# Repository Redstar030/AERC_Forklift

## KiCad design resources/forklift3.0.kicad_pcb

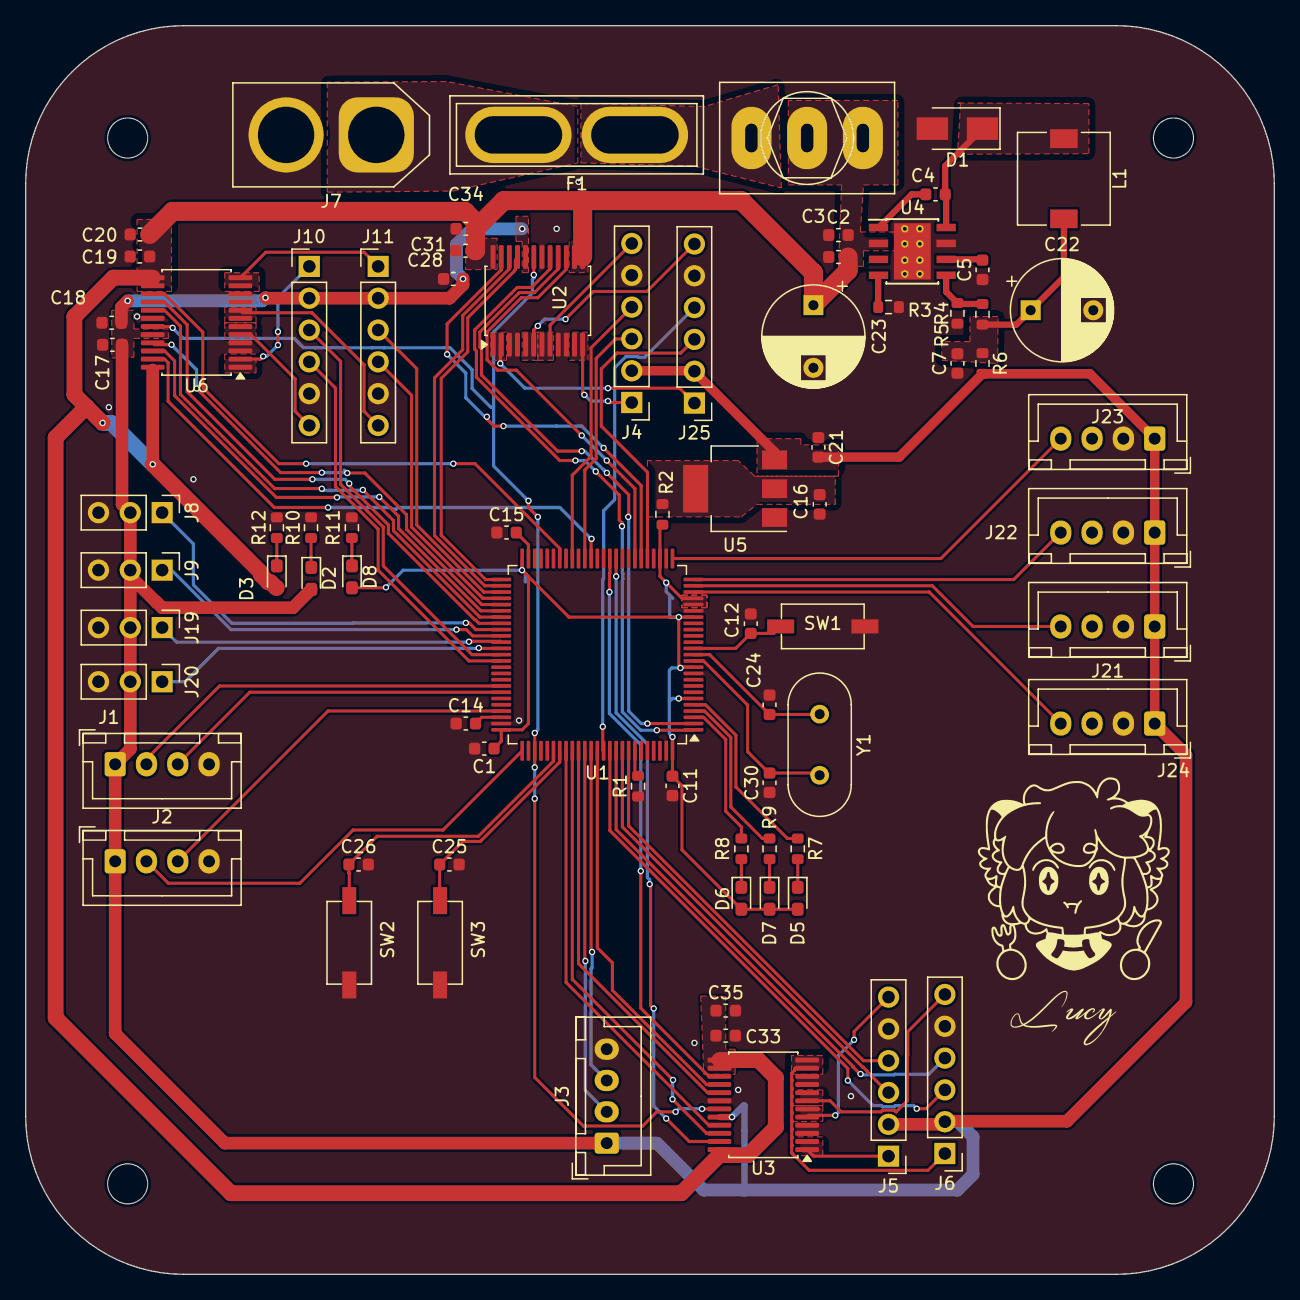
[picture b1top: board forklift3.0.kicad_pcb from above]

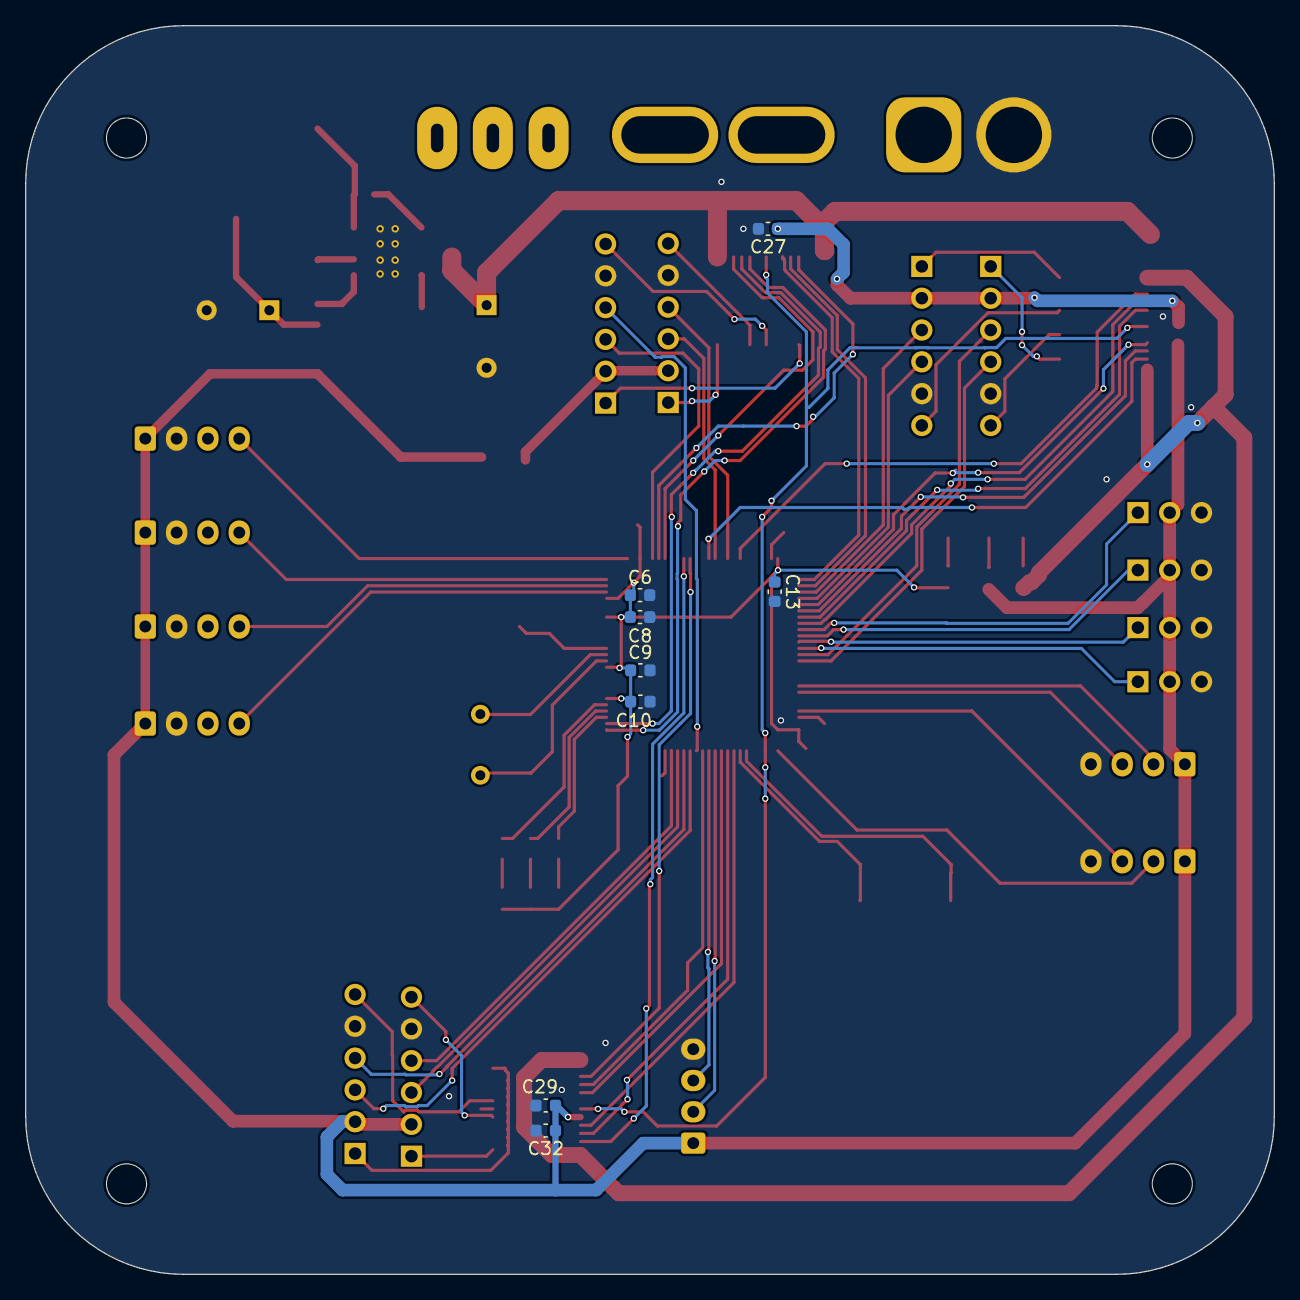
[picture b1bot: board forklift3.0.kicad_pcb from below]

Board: 2 copper layers, 99.7 x 99.7 mm, 89 parts (8 on the bottom side), 87 nets.

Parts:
C1, C4, C6, C8, C9, C10, C11, C12, C13, C25, C26: 100nF; C_0603_1608Metric
C2, C3, C14, C15: 2.2uF; C_0603_1608Metric
C5, C7: 39pF; C_0603_1608Metric
C16, C18, C20, C21, C28, C32, C34, C35: 10uF; C_0603_1608Metric
C17, C19, C27, C29, C31, C33: 0.1uF; C_0603_1608Metric
C22: 1MF; CP_Radial_D8.0mm_P12.00mm
C23: 50 100uF; CP_Radial_D8.0mm_P12.00mm
C24, C30: 20pF; C_0603_1608Metric
D1: SS54; D_SMA
D2: 5V; LED_0603_1608Metric_Pad1.05x0.95mm_HandSolder
D3: 12V; LED_0603_1608Metric_Pad1.05x0.95mm_HandSolder
D5: LED1; LED_0603_1608Metric_Pad1.05x0.95mm_HandSolder
D6: LED3; LED_0603_1608Metric_Pad1.05x0.95mm_HandSolder
D7: LED4; LED_0603_1608Metric_Pad1.05x0.95mm_HandSolder
D8: 3.3V; LED_0603_1608Metric_Pad1.05x0.95mm_HandSolder
F1: Fuse_Small; Fuse_Blade_ATO_directSolder
H1, H2, H3, H4: MountingHole; MountingHole_3.2mm_M3
J1, J2, J3, J21, J22, J23, J24: Conn_01x04; JST_XH_B4B-XH-A_1x04_P2.50mm_Vertical
J4, J5, J6, J10, J11, J25: Conn_01x06; PinHeader_1x06_P2.54mm_Vertical
J7: Conn_01x02; AMASS_XT60-M_1x02_P7.20mm_Vertical
J8, J9, J19, J20: Conn_01x03; PinHeader_1x03_P2.54mm_Vertical
L1: 22uH; L_7.3x7.3_H3.5
R1: 10K; R_0603_1608Metric
R2, R6: 0R; R_0603_1608Metric
R3: 162K; R_0603_1608Metric
R4: 53.6K; R_0603_1608Metric
R5: 10.2K; R_0603_1608Metric
R7, R8, R9, R10: 1.5K; R_0603_1608Metric
R11: 1K; R_0603_1608Metric
R12: 2K; R_0603_1608Metric
SW1: RST; SW_Push
SW2: But1; SW_Push
SW3: But2; SW_Push
SW4: SW_SPDT; SW_Toggle_Blue_wSlots
U1: STM32F407VETx; LQFP-100_14x14mm_P0.5mm
U2, U3, U6: TB6612FNG; SSOP-24_5.3x8.2mm_P0.65mm
U4: TPS54360DDA; TI_SO-PowerPAD-8_ThermalVias
U5: LM1117-3.3V; SOT-223
Y1: 8MHz; Crystal_HC49-4H_Vertical

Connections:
+3.3V: C1.1, C6.1, C8.1, C9.1, C10.1, C11.1, C13.1, D5.2 (A), D6.2 (A), D7.2 (A), D8.2 (A), R2.2, U1.6 (VBAT), U1.11 (VDD), U1.19 (VDD), U1.21 (VREF+), U1.22 (VDDA), U1.28 (VDD), U1.50 (VDD), U1.75 (VDD), U1.100 (VDD)
+5V: C17.1, C18.1, C21.2, C27.1, C28.1, C29.1, C32.1, D2.2 (A), J1.1, J2.1, J3.1, J4.2, J5.2, J6.2, J8.2, J9.2, J10.2, J11.2, J19.2, J20.2, J21.1, J22.1, J23.1, J24.1, J25.2, R6.2, U2.20 (VCC), U3.20 (VCC), U5.3 (VI), U6.20 (VCC)
+12V: C2.2, C3.2, C19.1, C20.1, C23.1, C31.1, C33.1, C34.1, C35.1, D3.2 (A), SW4.2 (B), SW4.3 (C), U2.13 (VM2), U2.14 (VM3), U2.24 (VM1), U3.13 (VM2), U3.14 (VM3), U3.24 (VM1), U4.2 (VIN), U6.13 (VM2), U6.14 (VM3), U6.24 (VM1)
/But1: C26.1, SW2.1, U1.81 (PD0)
/But2: C25.1, SW3.1, U1.82 (PD1)
/FB: R4.2, R5.1, U4.5 (FB)
/LED1: R7.1, U1.5 (PE6)
/LED3: R8.1, U1.3 (PE4)
/LED4: R9.1, U1.4 (PE5)
/M1_01: J25.1, U2.1 (AO1), U2.2 (AO1)
/M1_02: J25.6, U2.5 (AO2), U2.6 (AO2)
/M2_01: J4.1, U2.11 (BO1), U2.12 (BO1)
/M2_02: J4.6, U2.7 (BO2), U2.8 (BO2)
/M3_01: J5.1, U3.1 (AO1), U3.2 (AO1)
/M3_02: J5.6, U3.5 (AO2), U3.6 (AO2)
/M4_01: J6.1, U3.11 (BO1), U3.12 (BO1)
/M4_02: J6.6, U3.7 (BO2), U3.8 (BO2)
/M5_01: J10.1, U6.1 (AO1), U6.2 (AO1)
/M5_02: J10.6, U6.5 (AO2), U6.6 (AO2)
/M6_01: J11.1, U6.11 (BO1), U6.12 (BO1)
/M6_02: J11.6, U6.7 (BO2), U6.8 (BO2)
/PA0: J24.4, U1.23 (PA0)
/PA1: J21.4, U1.24 (PA1)
/PA2: J22.4, U1.25 (PA2)
/PA3: J23.4, U1.26 (PA3)
/PA5: J25.3, U1.30 (PA5)
/PB3: J25.4, U1.89 (PB3)
/PB4: J6.3, U1.90 (PB4)
/PB5: J6.4, U1.91 (PB5)
/PB6: J5.3, U1.92 (PB6)
/PB7: J5.4, U1.93 (PB7)
/PB12: U1.51 (PB12), U2.21 (AIN1)
/PB13: U1.52 (PB13), U2.22 (AIN2)
/PB14: J11.3, U1.53 (PB14)
/PB15: J11.4, U1.54 (PB15)
/PC6: J10.3, U1.63 (PC6)
/PC7: J10.4, U1.64 (PC7)
/PD2: U1.83 (PD2), U3.21 (AIN1)
/PD3: U1.84 (PD3), U3.22 (AIN2)
/PD4: U1.85 (PD4), U3.17 (BIN1)
/PD7: U1.88 (PD7), U3.16 (BIN2)
/PD8: U1.55 (PD8), U6.21 (AIN1)
/PD9: U1.56 (PD9), U6.22 (AIN2)
/PD10: U1.57 (PD10), U6.17 (BIN1)
/PD11: U1.58 (PD11), U6.16 (BIN2)
/PE2: U1.1 (PE2), U2.17 (BIN1)
/PE3: U1.2 (PE3), U2.16 (BIN2)
/PE9: J4.3, U1.40 (PE9)
/PE11: J4.4, U1.42 (PE11)
/PWM1: U1.31 (PA6), U2.23 (PWMA)
/PWM2: U1.32 (PA7), U2.15 (PWMB)
/PWM3: U1.35 (PB0), U3.23 (PWMA)
/PWM4: U1.36 (PB1), U3.15 (PWMB)
/PWM5: U1.39 (PE8), U6.23 (PWMA)
/PWM6: U1.44 (PE13), U6.15 (PWMB)
/PWMA: J8.1, U1.59 (PD12)
/PWMB: J9.1, U1.60 (PD13)
/PWMC: J19.1, U1.61 (PD14)
/PWMD: J20.1, U1.62 (PD15)
/STBY1: U1.78 (PC10), U2.19 (STBY), U3.19 (STBY), U6.19 (STBY)
/SWCLK: J2.2, U1.76 (PA14)
/SWDIO: J2.3, U1.72 (PA13)
/UART1_RX: J1.3, U1.69 (PA10)
/UART1_TX: J1.2, U1.68 (PA9)
/UART2_RX: J3.3, U1.87 (PD6)
/UART2_TX: J3.2, U1.86 (PD5)
GND: C1.2, C2.1, C3.1, C5.1, C6.2, C7.1, C8.2, C9.2, C10.2, C11.2, C12.1, C13.2, C14.1, C15.1, C16.1, C17.2, C18.2, C19.2, C20.2, C21.1, C22.2, C23.2, C24.1, C25.2, C26.2, C27.2, C28.2, C29.2, C30.1, C31.2, C32.2, C33.2, C34.2, C35.2, D1.2 (A), J1.4, J2.4, J3.4, J4.5, J5.5, J6.5, J7.2, J8.3, J9.3, J10.5, J11.5, J19.3, J20.3, J21.2, J22.2, J23.2, J24.2, J25.5, R1.1, R3.2, R5.2, R10.2, R11.2, R12.2, SW1.2, SW2.2, SW3.2, U1.10 (VSS), U1.20 (VSSA), U1.27 (VSS), U1.74 (VSS), U1.99 (VSS), U2.3 (PGND1), U2.4 (PGND1), U2.9 (PGND2), U2.10 (PGND2), U2.18 (GND), U3.3 (PGND1), U3.4 (PGND1), U3.9 (PGND2), U3.10 (PGND2), U3.18 (GND), U4.7 (GND), U4.9 (GNDPAD), U5.1 (GND), U6.3 (PGND1), U6.4 (PGND1), U6.9 (PGND2), U6.10 (PGND2), U6.18 (GND)
unnamed: C7.2, C22.1, L1.2, R4.1, R6.1
unnamed: C4.1, D1.1 (K), L1.1, U4.8 (SW)
unnamed: D2.1 (K), R10.1
unnamed: D3.1 (K), R12.1
unnamed: D5.1 (K), R7.2
unnamed: D6.1 (K), R8.2
unnamed: D7.1 (K), R9.2
unnamed: D8.1 (K), R11.1
unnamed: F1.2, J7.1
unnamed: F1.1, SW4.1 (A)
unnamed: R1.2, U1.94 (BOOT0)
unnamed: C12.2, SW1.1, U1.14 (NRST)
unnamed: C30.2, U1.12 (PH0), Y1.2
unnamed: C24.2, U1.13 (PH1), Y1.1
unnamed: C15.2, U1.49 (VCAP_1)
unnamed: C14.2, U1.73 (VCAP_2)
unnamed: C4.2, U4.1 (BOOT)
unnamed: C5.2, U4.6 (COMP)
unnamed: R3.1, U4.4 (RT/CLK)
unnamed: C16.2, R2.1, U5.2 (VO), U5.4 (Tab)

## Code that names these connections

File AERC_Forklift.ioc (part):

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Mcu.Name=STM32F407V(E-G)Tx
Mcu.Package=LQFP100
Mcu.UserName=STM32F407VETx
PA0-WKUP.GPIOParameters=GPIO_PuPd
PA0-WKUP.GPIO_PuPd=GPIO_PULLUP
PA0-WKUP.Signal=S_TIM5_CH1
PA1.GPIOParameters=GPIO_PuPd
PA1.GPIO_PuPd=GPIO_PULLUP
PA1.Signal=S_TIM5_CH2
PA10.Mode=Asynchronous
PA10.Signal=USART1_RX
PA13.Mode=Serial_Wire
PA13.Signal=SYS_JTMS-SWDIO
PA14.Mode=Serial_Wire
PA14.Signal=SYS_JTCK-SWCLK
PA5.GPIOParameters=GPIO_PuPd,GPIO_Label
PA5.GPIO_Label=ENC1A
PA5.GPIO_PuPd=GPIO_PULLUP
PA5.Signal=S_TIM2_CH1_ETR
PA6.GPIOParameters=GPIO_Label
PA6.GPIO_Label=M1_PWMA
PA6.Signal=S_TIM3_CH1
PA7.GPIOParameters=GPIO_Label
PA7.GPIO_Label=M1_PWMB
PA7.Signal=S_TIM3_CH2
PA9.Mode=Asynchronous
PA9.Signal=USART1_TX
PB0.GPIOParameters=GPIO_Label
PB0.GPIO_Label=M3_PWMA
PB0.Signal=S_TIM3_CH3
PB1.GPIOParameters=GPIO_Label
PB1.GPIO_Label=M3_PWMB
PB1.Signal=S_TIM3_CH4
PB12.GPIOParameters=GPIO_Label
PB12.GPIO_Label=M2_AIN1
PB12.Signal=GPIO_Output
PB13.GPIOParameters=GPIO_Label
PB13.GPIO_Label=M2_AIN2
PB13.Signal=GPIO_Output
PB14.GPIOParameters=GPIO_PuPd,GPIO_Label
PB14.GPIO_Label=ENC4A
PB14.GPIO_PuPd=GPIO_PULLUP
PB14.Signal=S_TIM12_CH1
PB15.GPIOParameters=GPIO_PuPd,GPIO_Label
PB15.GPIO_Label=ENC4B
PB15.GPIO_PuPd=GPIO_PULLUP
PB15.Signal=S_TIM12_CH2
PB3.GPIOParameters=GPIO_PuPd,GPIO_Label
PB3.GPIO_Label=ENC1B
PB3.GPIO_PuPd=GPIO_PULLUP
PB3.Signal=S_TIM2_CH2
PC10.GPIOParameters=PinState,GPIO_Label
PC10.GPIO_Label=STBY_ALL
PC10.PinState=GPIO_PIN_SET
PC10.Signal=GPIO_Output
PC6.GPIOParameters=GPIO_PuPd,GPIO_Label
PC6.GPIO_Label=ENC3A
PC6.GPIO_PuPd=GPIO_PULLUP
PC6.Signal=S_TIM8_CH1
PC7.GPIOParameters=GPIO_PuPd,GPIO_Label
PC7.GPIO_Label=ENC3B
PC7.GPIO_PuPd=GPIO_PULLUP
PC7.Signal=S_TIM8_CH2
PD0.GPIOParameters=GPIO_Label
PD0.GPIO_Label=But2
PD0.Signal=GPIO_Input
PD1.GPIOParameters=GPIO_Label
PD1.GPIO_Label=But1
PD1.Signal=GPIO_Input
PD10.GPIOParameters=GPIO_Label
PD10.GPIO_Label=slider2A
PD10.Signal=GPIO_Output
PD11.GPIOParameters=GPIO_Label
PD11.GPIO_Label=slider2B
PD11.Signal=GPIO_Output
PD2.GPIOParameters=GPIO_Label
PD2.GPIO_Label=M3_AIN1
PD2.Signal=GPIO_Output
PD3.GPIOParameters=GPIO_Label
PD3.GPIO_Label=M3_AIN2
PD3.Signal=GPIO_Output
PD4.GPIOParameters=GPIO_Label
PD4.GPIO_Label=M3_BIN1
PD4.Signal=GPIO_Output
PD5.Mode=Asynchronous
PD5.Signal=USART2_TX
PD6.Mode=Asynchronous
PD6.Signal=USART2_RX
PD7.GPIOParameters=GPIO_Label
PD7.GPIO_Label=M3_BIN2
PD7.Signal=GPIO_Output
PD8.GPIOParameters=GPIO_Label
PD8.GPIO_Label=slider1A
PD8.Signal=GPIO_Output
PD9.GPIOParameters=GPIO_Label
PD9.GPIO_Label=slider1B
PD9.Signal=GPIO_Output
PE13.GPIOParameters=GPIO_Label
PE13.GPIO_Label=fork2
PE13.Signal=GPIO_Output
PE2.GPIOParameters=GPIO_Label
PE2.GPIO_Label=M2_BIN1
PE2.Signal=GPIO_Output
PE3.GPIOParameters=GPIO_Label
PE3.GPIO_Label=M2_BIN2
PE3.Signal=GPIO_Output
PE4.GPIOParameters=GPIO_Label
PE4.GPIO_Label=LED3
PE4.Signal=GPIO_Output
PE5.GPIOParameters=GPIO_Label
PE5.GPIO_Label=LED4
PE5.Signal=GPIO_Output
PE6.GPIOParameters=GPIO_Label
PE6.GPIO_Label=LED1
PE6.Signal=GPIO_Output
PE8.GPIOParameters=GPIO_Label
PE8.GPIO_Label=fork1 
PE8.Signal=GPIO_Output
PE9.GPIOParameters=GPIO_PuPd,GPIO_Label
PE9.GPIO_Label=ENC2A
PE9.GPIO_PuPd=GPIO_PULLUP
PE9.Signal=S_TIM1_CH1
PH0-OSC_IN.Mode=HSE-External-Oscillator
PH0-OSC_IN.Signal=RCC_OSC_IN
PH1-OSC_OUT.Mode=HSE-External-Oscillator
PH1-OSC_OUT.Signal=RCC_OSC_OUT
RCC.HSE_VALUE=25000000
RCC.SYSCLKFreq_VALUE=16000000
board=custom

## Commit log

2026-04-12 intialization
2026-04-12 motor working
2026-04-12 encoder initialize
2026-04-12 encoder testing
2026-04-13 movable with controller.
2026-04-21 movable v1
2026-05-13 ps4 ini
2026-05-13 ps4 working
